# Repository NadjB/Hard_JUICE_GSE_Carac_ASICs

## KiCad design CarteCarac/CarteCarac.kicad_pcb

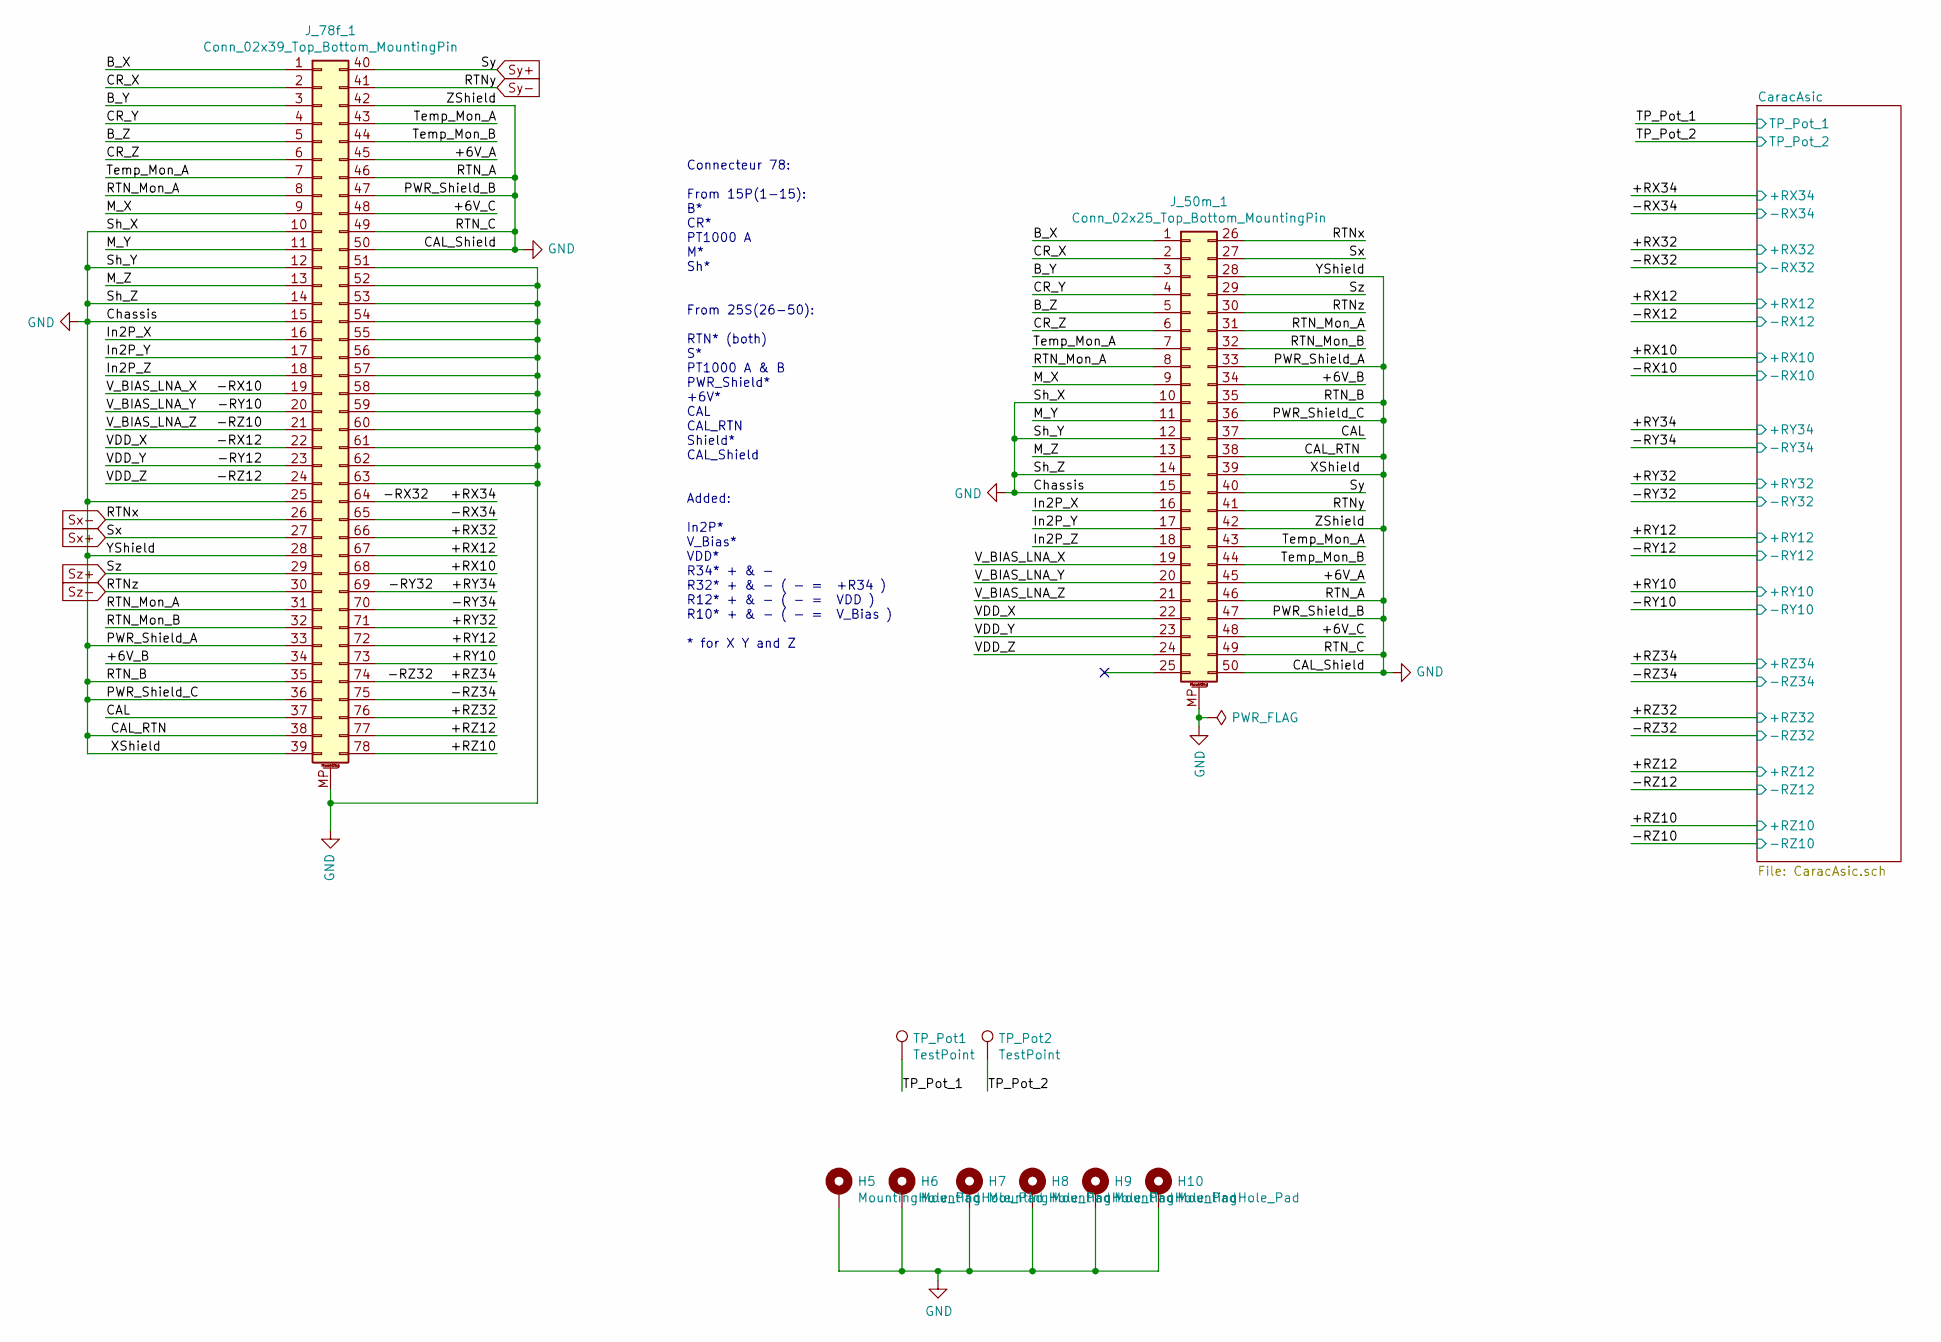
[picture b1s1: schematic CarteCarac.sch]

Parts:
H5, H6, H7, H8, H9, H10: MountingHole_Pad; MountingHole_3.2mm_M3_Pad_Via
J_50m_1: Conn_02x25_Top_Bottom_MountingPin; db_50m_MP_DD50S564TXLF
J_78f_1: Conn_02x39_Top_Bottom_MountingPin; db_78f_MP_09565527613
TP_Pot1, TP_Pot2: TestPoint; Banana_test_point_4mm

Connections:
/+6V_A: J_50m_1.45, J_78f_1.45
/+6V_B: J_50m_1.34, J_78f_1.34
/+6V_C: J_50m_1.48, J_78f_1.48
/+RX10: J_78f_1.68; also elsewhere on the board
/+RX12: J_78f_1.67; also elsewhere on the board
/+RX32: J_78f_1.66; also elsewhere on the board
/+RX34: J_78f_1.64; also elsewhere on the board
/+RY10: J_78f_1.73; also elsewhere on the board
/+RY12: J_78f_1.72; also elsewhere on the board
/+RY32: J_78f_1.71; also elsewhere on the board
/+RY34: J_78f_1.69; also elsewhere on the board
/+RZ10: J_78f_1.78; also elsewhere on the board
/+RZ12: J_78f_1.77; also elsewhere on the board
/+RZ32: J_78f_1.76; also elsewhere on the board
/+RZ34: J_78f_1.74; also elsewhere on the board
/-RX10: J_50m_1.19, J_78f_1.19; also elsewhere on the board
/-RX12: J_50m_1.22, J_78f_1.22; also elsewhere on the board
/-RX34: J_78f_1.65; also elsewhere on the board
/-RY10: J_50m_1.20, J_78f_1.20; also elsewhere on the board
/-RY12: J_50m_1.23, J_78f_1.23; also elsewhere on the board
/-RY34: J_78f_1.70; also elsewhere on the board
/-RZ10: J_50m_1.21, J_78f_1.21; also elsewhere on the board
/-RZ12: J_50m_1.24, J_78f_1.24; also elsewhere on the board
/-RZ34: J_78f_1.75; also elsewhere on the board
/B_X: J_50m_1.1, J_78f_1.1
/B_Y: J_50m_1.3, J_78f_1.3
/B_Z: J_50m_1.5, J_78f_1.5
/CAL: J_50m_1.37, J_78f_1.37
/CR_X: J_50m_1.2, J_78f_1.2
/CR_Y: J_50m_1.4, J_78f_1.4
/CR_Z: J_50m_1.6, J_78f_1.6
/In2P_X: J_50m_1.16, J_78f_1.16
/In2P_Y: J_50m_1.17, J_78f_1.17
/In2P_Z: J_50m_1.18, J_78f_1.18
/M_X: J_50m_1.9, J_78f_1.9
/M_Y: J_50m_1.11, J_78f_1.11
/M_Z: J_50m_1.13, J_78f_1.13
/RTN_Mon_A: J_50m_1.8, J_50m_1.31, J_78f_1.8, J_78f_1.31
/RTN_Mon_B: J_50m_1.32, J_78f_1.32
/TP_Pot_1: TP_Pot1.1; also elsewhere on the board
/TP_Pot_2: TP_Pot2.1; also elsewhere on the board
/Temp_Mon_A: J_50m_1.7, J_50m_1.43, J_78f_1.7, J_78f_1.43
/Temp_Mon_B: J_50m_1.44, J_78f_1.44
GND: H5.1, H6.1, H7.1, H8.1, H9.1, H10.1, J_50m_1.10, J_50m_1.12, J_50m_1.14, J_50m_1.15, J_50m_1.28, J_50m_1.33, J_50m_1.35, J_50m_1.36, J_50m_1.38, J_50m_1.39, J_50m_1.42, J_50m_1.46, J_50m_1.47, J_50m_1.49, J_50m_1.50, J_50m_1.MP (MountPin), J_78f_1.10, J_78f_1.12, J_78f_1.14, J_78f_1.15, J_78f_1.25, J_78f_1.28, J_78f_1.33, J_78f_1.35, J_78f_1.36, J_78f_1.38, J_78f_1.39, J_78f_1.42, J_78f_1.46, J_78f_1.47, J_78f_1.49, J_78f_1.50, J_78f_1.51, J_78f_1.52, J_78f_1.53, J_78f_1.54, J_78f_1.55, J_78f_1.56, J_78f_1.57, J_78f_1.58, J_78f_1.59, J_78f_1.60, J_78f_1.61, J_78f_1.62, J_78f_1.63, J_78f_1.MP (MountPin); also elsewhere on the board
Sx+: J_50m_1.27, J_78f_1.27
Sx-: J_50m_1.26, J_78f_1.26
Sy+: J_50m_1.40, J_78f_1.40
Sy-: J_50m_1.41, J_78f_1.41
Sz+: J_50m_1.29, J_78f_1.29
Sz-: J_50m_1.30, J_78f_1.30

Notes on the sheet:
Connecteur 78: From 15P(1-15): B* CR* PT1000 A M* Sh* From 25S(26-50): RTN* (both) S* PT1000 A & B PWR_Shield* +6V* CAL CAL_RTN Shield* CAL_Shield Added: In2P* V_Bias* VDD* R34* + & - R32* + & - ( - = +R34 ) R12* + & - ( - = VDD ) R10* + & - ( - = V_Bias ) * for X Y and Z

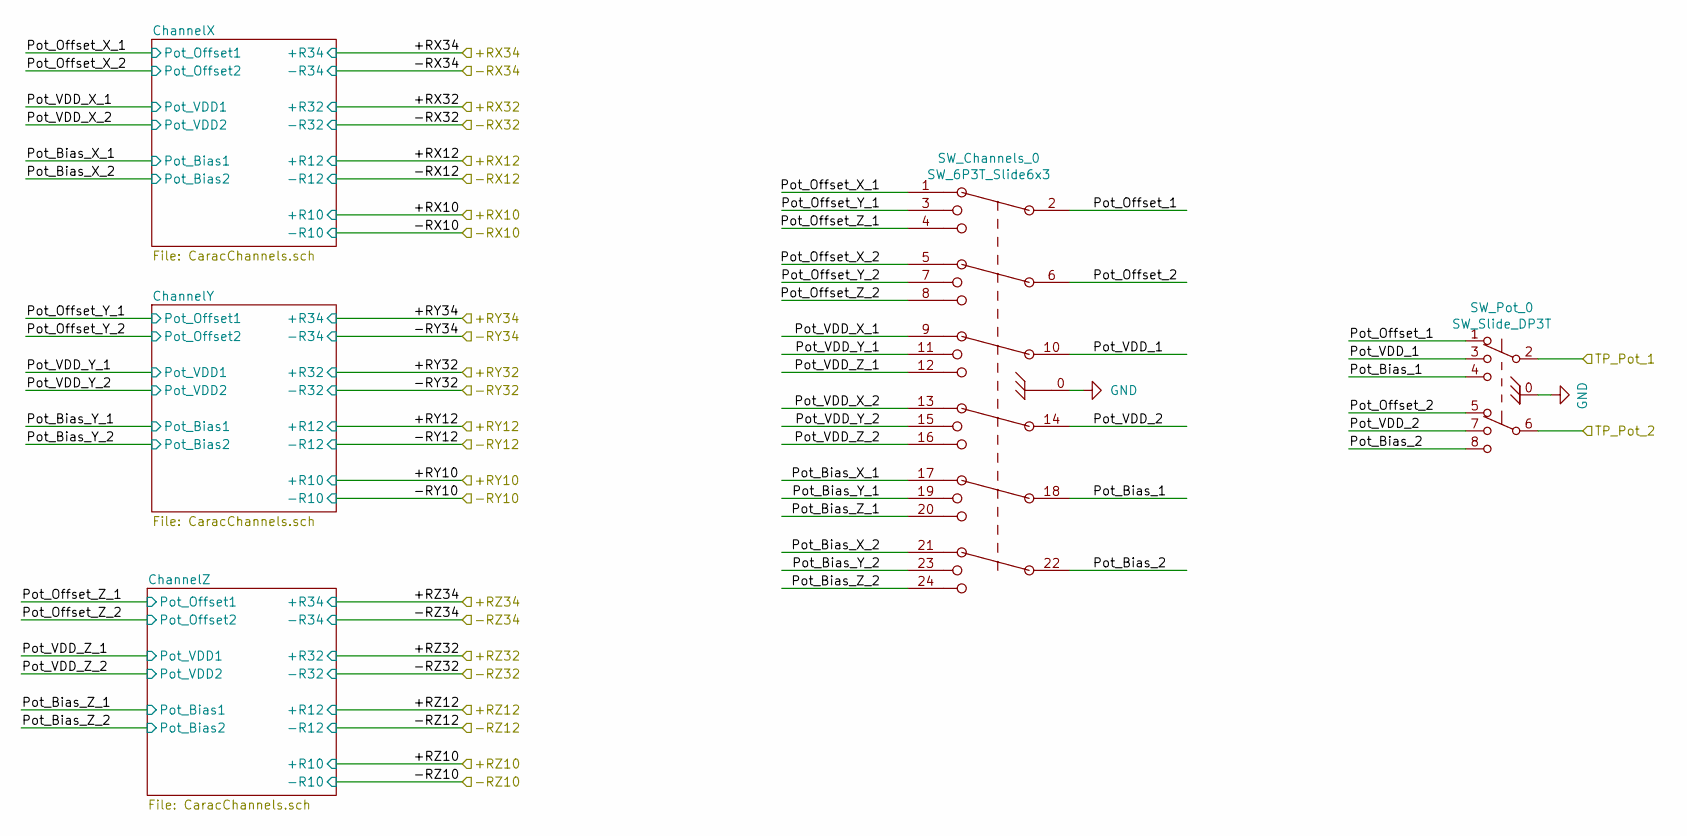
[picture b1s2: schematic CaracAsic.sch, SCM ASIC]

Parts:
SW_Channels_0: SW_6P3T_Slide6x3; SW_6P3T_MSS6350R04_TE
SW_Pot_0: SW_Slide_DP3T; MHS233K_DP3T_Slide_Switch

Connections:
/CaracAsic/Pot_Bias_1: SW_Channels_0.18, SW_Pot_0.4 (D)
/CaracAsic/Pot_Bias_2: SW_Channels_0.22, SW_Pot_0.8 (D)
/CaracAsic/Pot_Bias_X_1: SW_Channels_0.17; also elsewhere on the board
/CaracAsic/Pot_Bias_X_2: SW_Channels_0.21; also elsewhere on the board
/CaracAsic/Pot_Bias_Y_1: SW_Channels_0.19; also elsewhere on the board
/CaracAsic/Pot_Bias_Y_2: SW_Channels_0.23; also elsewhere on the board
/CaracAsic/Pot_Bias_Z_1: SW_Channels_0.20; also elsewhere on the board
/CaracAsic/Pot_Bias_Z_2: SW_Channels_0.24; also elsewhere on the board
/CaracAsic/Pot_Offset_1: SW_Channels_0.2, SW_Pot_0.1 (A)
/CaracAsic/Pot_Offset_2: SW_Channels_0.6, SW_Pot_0.5 (A)
/CaracAsic/Pot_Offset_X_1: SW_Channels_0.1; also elsewhere on the board
/CaracAsic/Pot_Offset_X_2: SW_Channels_0.5; also elsewhere on the board
/CaracAsic/Pot_Offset_Y_1: SW_Channels_0.3; also elsewhere on the board
/CaracAsic/Pot_Offset_Y_2: SW_Channels_0.7; also elsewhere on the board
/CaracAsic/Pot_Offset_Z_1: SW_Channels_0.4; also elsewhere on the board
/CaracAsic/Pot_Offset_Z_2: SW_Channels_0.8; also elsewhere on the board
/CaracAsic/Pot_VDD_1: SW_Channels_0.10, SW_Pot_0.3 (B)
/CaracAsic/Pot_VDD_2: SW_Channels_0.14, SW_Pot_0.7 (B)
/CaracAsic/Pot_VDD_X_1: SW_Channels_0.9; also elsewhere on the board
/CaracAsic/Pot_VDD_X_2: SW_Channels_0.13; also elsewhere on the board
/CaracAsic/Pot_VDD_Y_1: SW_Channels_0.11; also elsewhere on the board
/CaracAsic/Pot_VDD_Y_2: SW_Channels_0.15; also elsewhere on the board
/CaracAsic/Pot_VDD_Z_1: SW_Channels_0.12; also elsewhere on the board
/CaracAsic/Pot_VDD_Z_2: SW_Channels_0.16; also elsewhere on the board
/TP_Pot_1: SW_Pot_0.2 (C); also elsewhere on the board
/TP_Pot_2: SW_Pot_0.6 (C); also elsewhere on the board
GND: SW_Channels_0.0, SW_Pot_0.0 (Casing); also elsewhere on the board

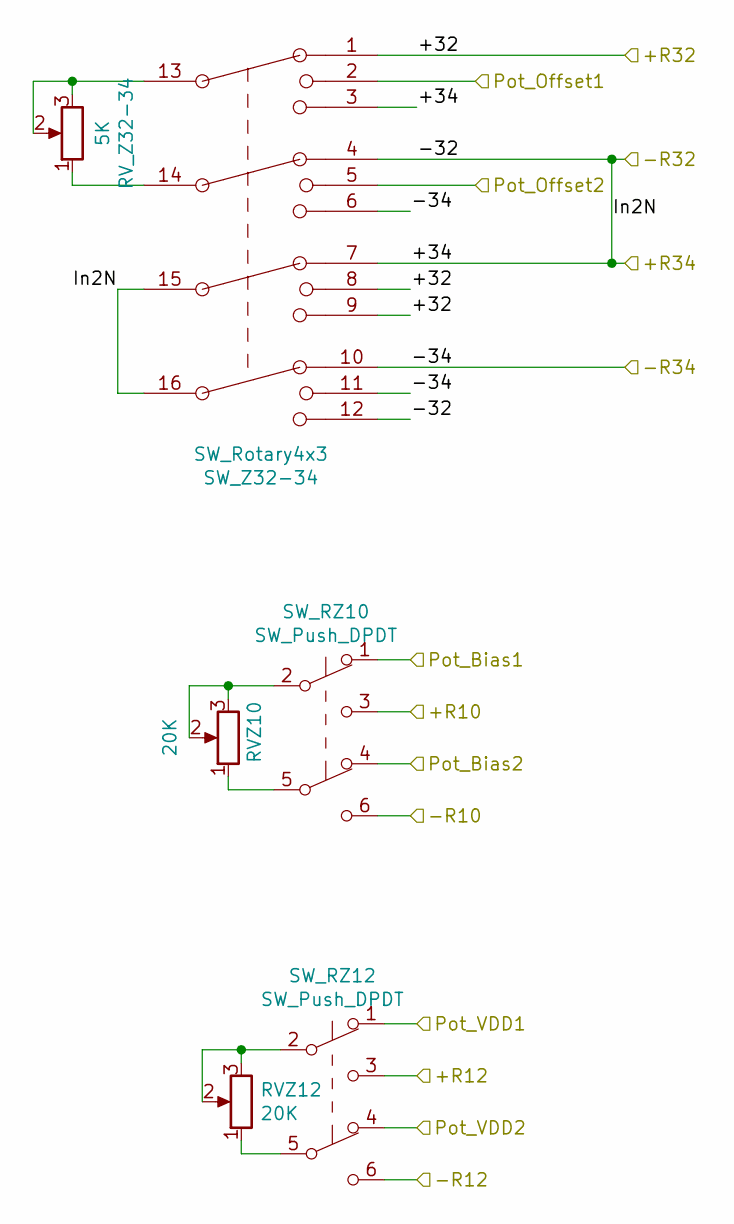
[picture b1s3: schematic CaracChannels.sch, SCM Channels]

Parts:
RVX10, RVX12: 20K; Potentiometer_Bourns_3683S
RV_X32-34: 5K; Potentiometer_Bourns_3683S
SW_RX10, SW_RX12: SW_Push_DPDT; SW_NKK_DPDT_B22AP
SW_X32-34: SW_Rotary4x3; Switch_4P3T_MRA403_NKK_Turned30°

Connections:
/+RX10: SW_RX10.3 (C); also elsewhere on the board
/+RX12: SW_RX12.3 (C); also elsewhere on the board
/+RX32: SW_X32-34.1, SW_X32-34.8, SW_X32-34.9; also elsewhere on the board
/+RX34: SW_X32-34.3, SW_X32-34.4, SW_X32-34.7, SW_X32-34.12, SW_X32-34.15, SW_X32-34.16; also elsewhere on the board
/-RX10: SW_RX10.6 (C); also elsewhere on the board
/-RX12: SW_RX12.6 (C); also elsewhere on the board
/-RX34: SW_X32-34.6, SW_X32-34.10, SW_X32-34.11; also elsewhere on the board
/CaracAsic/Pot_Bias_X_1: SW_RX10.1 (A); also elsewhere on the board
/CaracAsic/Pot_Bias_X_2: SW_RX10.4 (A); also elsewhere on the board
/CaracAsic/Pot_Offset_X_1: SW_X32-34.2; also elsewhere on the board
/CaracAsic/Pot_Offset_X_2: SW_X32-34.5; also elsewhere on the board
/CaracAsic/Pot_VDD_X_1: SW_RX12.1 (A); also elsewhere on the board
/CaracAsic/Pot_VDD_X_2: SW_RX12.4 (A); also elsewhere on the board
unnamed: RVX10.1, SW_RX10.5 (B)
unnamed: RVX10.2, RVX10.3, SW_RX10.2 (B)
unnamed: RVX12.1, SW_RX12.5 (B)
unnamed: RVX12.2, RVX12.3, SW_RX12.2 (B)
unnamed: RV_X32-34.1, SW_X32-34.14
unnamed: RV_X32-34.2, RV_X32-34.3, SW_X32-34.13

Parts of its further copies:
RVY10, RVY12: 20K; Potentiometer_Bourns_3683S
RVZ10, RVZ12: 20K; Potentiometer_Bourns_3683S
RV_Y32-34: 5K; Potentiometer_Bourns_3683S
RV_Z32-34: 5K; Potentiometer_Bourns_3683S
SW_RY10, SW_RY12: SW_Push_DPDT; SW_NKK_DPDT_B22AP
SW_RZ10, SW_RZ12: SW_Push_DPDT; SW_NKK_DPDT_B22AP
SW_Y32-34: SW_Rotary4x3; Switch_4P3T_MRA403_NKK_Turned30°
SW_Z32-34: SW_Rotary4x3; Switch_4P3T_MRA403_NKK_Turned30°

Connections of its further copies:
/+RY10: SW_RY10.3 (C); also elsewhere on the board
/+RY12: SW_RY12.3 (C); also elsewhere on the board
/+RY32: SW_Y32-34.1, SW_Y32-34.8, SW_Y32-34.9; also elsewhere on the board
/+RY34: SW_Y32-34.3, SW_Y32-34.4, SW_Y32-34.7, SW_Y32-34.12, SW_Y32-34.15, SW_Y32-34.16; also elsewhere on the board
/+RZ10: SW_RZ10.3 (C); also elsewhere on the board
/+RZ12: SW_RZ12.3 (C); also elsewhere on the board
/+RZ32: SW_Z32-34.1, SW_Z32-34.8, SW_Z32-34.9; also elsewhere on the board
/+RZ34: SW_Z32-34.3, SW_Z32-34.4, SW_Z32-34.7, SW_Z32-34.12, SW_Z32-34.15, SW_Z32-34.16; also elsewhere on the board
/-RY10: SW_RY10.6 (C); also elsewhere on the board
/-RY12: SW_RY12.6 (C); also elsewhere on the board
/-RY34: SW_Y32-34.6, SW_Y32-34.10, SW_Y32-34.11; also elsewhere on the board
/-RZ10: SW_RZ10.6 (C); also elsewhere on the board
/-RZ12: SW_RZ12.6 (C); also elsewhere on the board
/-RZ34: SW_Z32-34.6, SW_Z32-34.10, SW_Z32-34.11; also elsewhere on the board
/CaracAsic/Pot_Bias_Y_1: SW_RY10.1 (A); also elsewhere on the board
/CaracAsic/Pot_Bias_Y_2: SW_RY10.4 (A); also elsewhere on the board
/CaracAsic/Pot_Bias_Z_1: SW_RZ10.1 (A); also elsewhere on the board
/CaracAsic/Pot_Bias_Z_2: SW_RZ10.4 (A); also elsewhere on the board
/CaracAsic/Pot_Offset_Y_1: SW_Y32-34.2; also elsewhere on the board
/CaracAsic/Pot_Offset_Y_2: SW_Y32-34.5; also elsewhere on the board
/CaracAsic/Pot_Offset_Z_1: SW_Z32-34.2; also elsewhere on the board
/CaracAsic/Pot_Offset_Z_2: SW_Z32-34.5; also elsewhere on the board
/CaracAsic/Pot_VDD_Y_1: SW_RY12.1 (A); also elsewhere on the board
/CaracAsic/Pot_VDD_Y_2: SW_RY12.4 (A); also elsewhere on the board
/CaracAsic/Pot_VDD_Z_1: SW_RZ12.1 (A); also elsewhere on the board
/CaracAsic/Pot_VDD_Z_2: SW_RZ12.4 (A); also elsewhere on the board
unnamed: RVY10.1, SW_RY10.5 (B)
unnamed: RVY10.2, RVY10.3, SW_RY10.2 (B)
unnamed: RVY12.1, SW_RY12.5 (B)
unnamed: RVY12.2, RVY12.3, SW_RY12.2 (B)
unnamed: RVZ10.1, SW_RZ10.5 (B)
unnamed: RVZ10.2, RVZ10.3, SW_RZ10.2 (B)
unnamed: RVZ12.1, SW_RZ12.5 (B)
unnamed: RVZ12.2, RVZ12.3, SW_RZ12.2 (B)
unnamed: RV_Y32-34.1, SW_Y32-34.14
unnamed: RV_Y32-34.2, RV_Y32-34.3, SW_Y32-34.13
unnamed: RV_Z32-34.1, SW_Z32-34.14
unnamed: RV_Z32-34.2, RV_Z32-34.3, SW_Z32-34.13

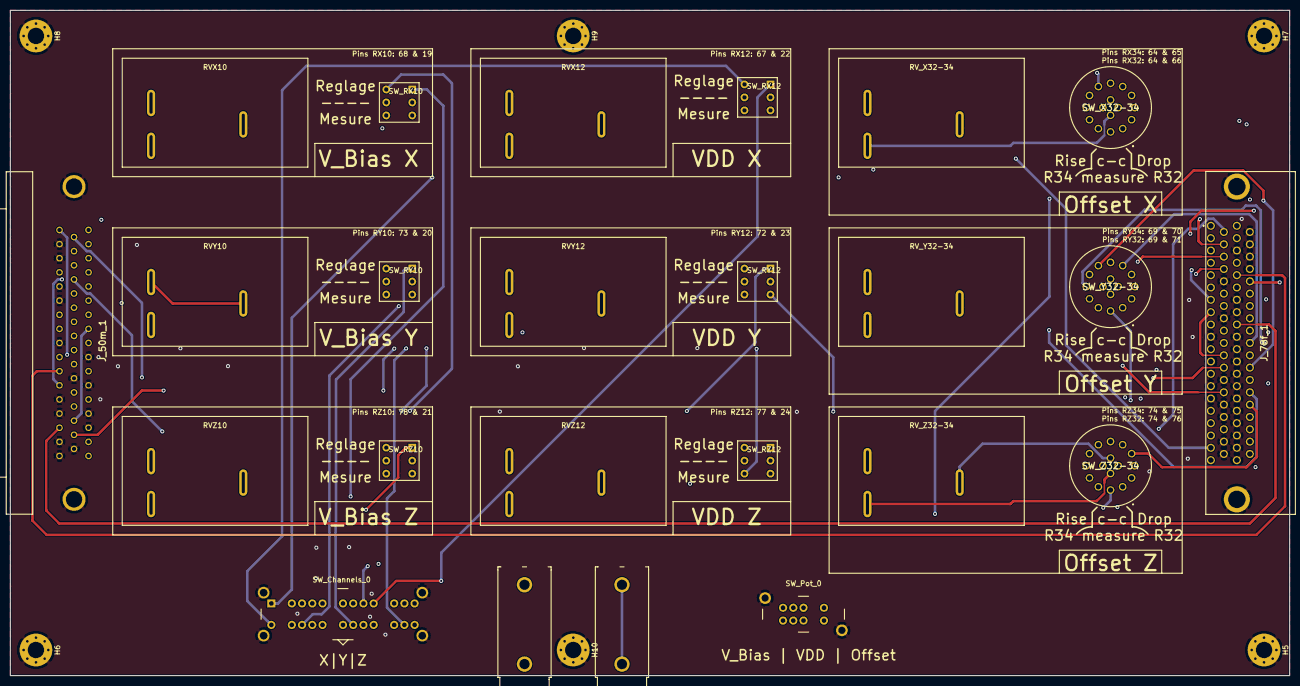
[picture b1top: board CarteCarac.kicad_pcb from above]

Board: 4 copper layers, 250.0 x 130.0 mm, 30 parts (0 on the bottom side), 92 nets.

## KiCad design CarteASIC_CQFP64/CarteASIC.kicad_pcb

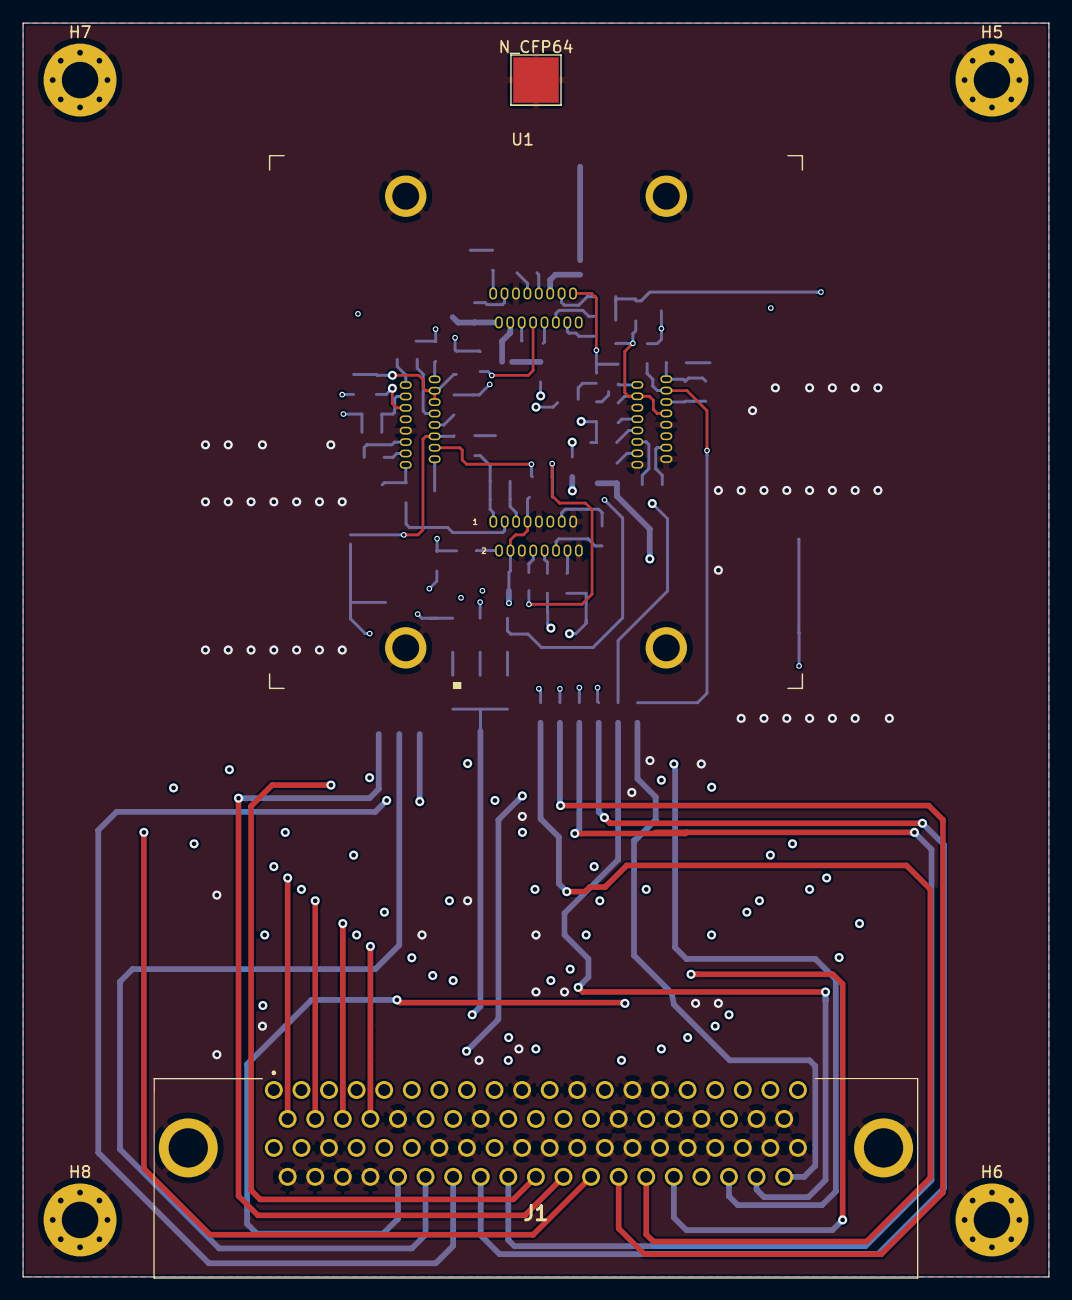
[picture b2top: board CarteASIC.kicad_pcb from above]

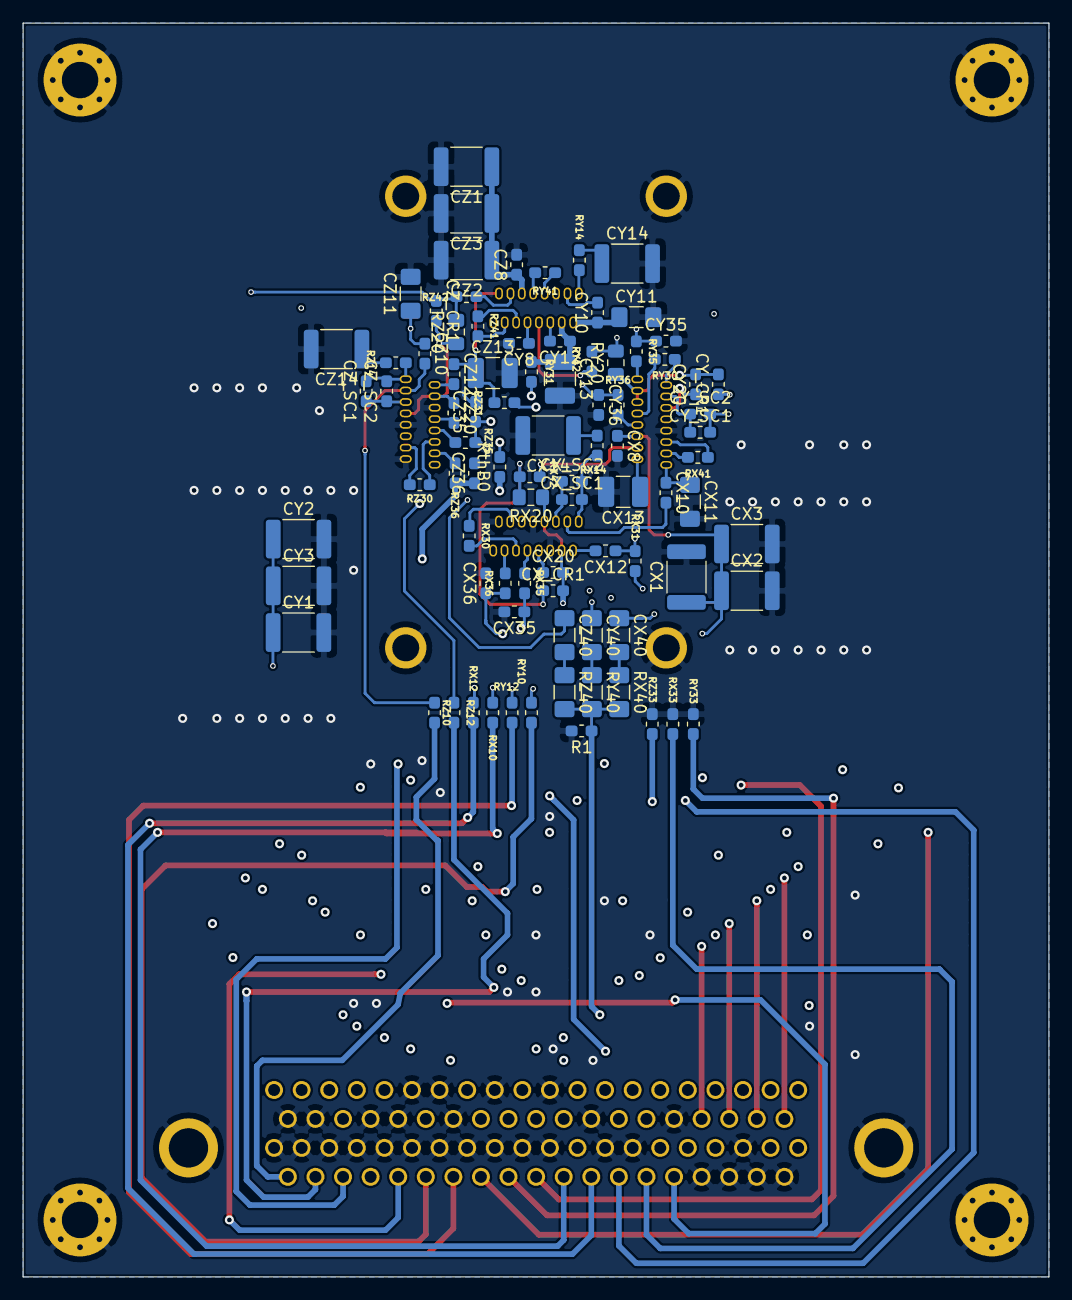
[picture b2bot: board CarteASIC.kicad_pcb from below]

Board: 4 copper layers, 90.0 x 110.0 mm, 93 parts (86 on the bottom side), 84 nets.

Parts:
CX1, CX2, CX3: 680n; C_1812_4532Metric_Pad1.30x3.40mm_HandSolder
CX8: 1n; C_0603_1608Metric_Pad1.05x0.95mm_HandSolder
CX10, CX12: 221p; C_0603_1608Metric_Pad1.05x0.95mm_HandSolder
CX11, CX40: 220n; C_1206_3216Metric_Pad1.42x1.75mm_HandSolder
CX13: 470n; C_1210_3225Metric_Pad1.42x2.65mm_HandSolder
CX14: 470n; C_1812_4532Metric_Pad1.30x3.40mm_HandSolder
CX20, CX35, CX36: *; C_0603_1608Metric_Pad1.05x0.95mm_HandSolder
CX_CR1: 150p; C_0603_1608Metric_Pad1.05x0.95mm_HandSolder
CX_SC1, CX_SC2: *; C_0603_1608Metric_Pad1.05x0.95mm_HandSolder
CY1, CY2, CY3: 680n; C_1812_4532Metric_Pad1.30x3.40mm_HandSolder
CY8: 1n; C_0603_1608Metric_Pad1.05x0.95mm_HandSolder
CY10, CY12: 221p; C_0603_1608Metric_Pad1.05x0.95mm_HandSolder
CY11, CY40: 220n; C_1206_3216Metric_Pad1.42x1.75mm_HandSolder
CY13: 470n; C_1210_3225Metric_Pad1.42x2.65mm_HandSolder
CY14: 470n; C_1812_4532Metric_Pad1.30x3.40mm_HandSolder
CY20, CY35, CY36: *; C_0603_1608Metric_Pad1.05x0.95mm_HandSolder
CY_CR1: 150p; C_0603_1608Metric_Pad1.05x0.95mm_HandSolder
CY_SC1, CY_SC2: *; C_0603_1608Metric_Pad1.05x0.95mm_HandSolder
CZ1, CZ2, CZ3: 680n; C_1812_4532Metric_Pad1.30x3.40mm_HandSolder
CZ8: 1n; C_0603_1608Metric_Pad1.05x0.95mm_HandSolder
CZ10, CZ12: 221p; C_0603_1608Metric_Pad1.05x0.95mm_HandSolder
CZ11, CZ40: 220n; C_1206_3216Metric_Pad1.42x1.75mm_HandSolder
CZ13: 470n; C_1210_3225Metric_Pad1.42x2.65mm_HandSolder
CZ14: 470n; C_1812_4532Metric_Pad1.30x3.40mm_HandSolder
CZ20, CZ35, CZ36: *; C_0603_1608Metric_Pad1.05x0.95mm_HandSolder
CZ_CR1: 150p; C_0603_1608Metric_Pad1.05x0.95mm_HandSolder
CZ_SC1, CZ_SC2: *; C_0603_1608Metric_Pad1.05x0.95mm_HandSolder
H5, H6, H7, H8: MountingHole_Pad; MountingHole_3.2mm_M3_Pad_Via
J1: Conn_02x39_Top_Bottom_MountingPin; db_78m_09565627813
N_CFP64: Housing_Pad; TestPoint_Pad_4.0x4.0mm
R1: 10k; R_0603_1608Metric_Pad1.05x0.95mm_HandSolder
RX10: 22K; R_0603_1608Metric_Pad1.05x0.95mm_HandSolder
RX12: 44K; R_0603_1608Metric_Pad1.05x0.95mm_HandSolder
RX14: 400; R_0603_1608Metric_Pad1.05x0.95mm_HandSolder
RX20: 150k; R_0805_2012Metric_Pad1.15x1.40mm_HandSolder
RX30: 7,68k; R_0603_1608Metric_Pad1.05x0.95mm_HandSolder
RX31, RX33: 49,9k; R_0603_1608Metric_Pad1.05x0.95mm_HandSolder
RX35, RX36: 49,9; R_0603_1608Metric_Pad1.05x0.95mm_HandSolder
RX40: 750k; R_1206_3216Metric_Pad1.42x1.75mm_HandSolder
RX41: 24,9k; R_0603_1608Metric_Pad1.05x0.95mm_HandSolder
RX42: 42,2k; R_0603_1608Metric_Pad1.05x0.95mm_HandSolder
RY10: 22K; R_0603_1608Metric_Pad1.05x0.95mm_HandSolder
RY12: 44K; R_0603_1608Metric_Pad1.05x0.95mm_HandSolder
RY14: 400; R_0603_1608Metric_Pad1.05x0.95mm_HandSolder
RY20: 150k; R_0805_2012Metric_Pad1.15x1.40mm_HandSolder
RY30: 7,68k; R_0603_1608Metric_Pad1.05x0.95mm_HandSolder
RY31, RY33: 49,9k; R_0603_1608Metric_Pad1.05x0.95mm_HandSolder
RY35, RY36: 49,9; R_0603_1608Metric_Pad1.05x0.95mm_HandSolder
RY40: 750k; R_1206_3216Metric_Pad1.42x1.75mm_HandSolder
RY41: 24,9k; R_0603_1608Metric_Pad1.05x0.95mm_HandSolder
RY42: 42,2k; R_0603_1608Metric_Pad1.05x0.95mm_HandSolder
RZ10: 22K; R_0603_1608Metric_Pad1.05x0.95mm_HandSolder
RZ12: 44K; R_0603_1608Metric_Pad1.05x0.95mm_HandSolder
RZ14: 400; R_0603_1608Metric_Pad1.05x0.95mm_HandSolder
RZ20: 150k; R_0805_2012Metric_Pad1.15x1.40mm_HandSolder
RZ30: 7,68k; R_0603_1608Metric_Pad1.05x0.95mm_HandSolder
RZ31, RZ33: 49,9k; R_0603_1608Metric_Pad1.05x0.95mm_HandSolder
RZ35, RZ36: 49,9; R_0603_1608Metric_Pad1.05x0.95mm_HandSolder
RZ40: 750k; R_1206_3216Metric_Pad1.42x1.75mm_HandSolder
RZ41: 24,9k; R_0603_1608Metric_Pad1.05x0.95mm_HandSolder
RZ42: 42,2k; R_0603_1608Metric_Pad1.05x0.95mm_HandSolder
RthB0: PT1000; R_0603_1608Metric_Pad1.05x0.95mm_HandSolder
U1: ASIC_JUICE; 8500-50mm-64T-Ovale-EuroCircuitOK

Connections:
/+6V_A: CX1.1, CX2.1, CX3.1, CX8.1, J1.45, U1.59
/+6V_B: CY1.1, CY2.1, CY3.1, CY8.1, J1.34, U1.39
/+6V_C: CZ1.1, CZ2.1, CZ3.1, CZ8.1, J1.48, U1.38
/+RX10: J1.68, RX10.2
/+RX12: J1.67, RX12.2
/+RX32: J1.66, RX31.1
/+RX34: J1.64, U1.11
/+RY10: J1.73, RY10.2
/+RY12: J1.72, RY12.2
/+RY32: J1.71, RY31.1
/+RY34: J1.69, U1.56
/+RZ10: J1.78, RZ10.2
/+RZ12: J1.77, RZ12.2
/+RZ32: J1.76, RZ31.1
/+RZ34: J1.74, U1.22
/-RX10: CX10.1, CX11.1, J1.19, U1.64
/-RX12: CX12.1, CX13.1, J1.22, RX31.2, U1.63
/-RX34: J1.65, RX33.1
/-RY10: CY10.1, CY11.1, J1.20, U1.47
/-RY12: CY12.1, CY13.1, J1.23, RY31.2, U1.45
/-RY34: J1.70, RY33.1
/-RZ10: CZ10.1, CZ11.1, J1.21, U1.33
/-RZ12: CZ12.1, CZ13.1, J1.24, RZ31.2, U1.34
/-RZ34: J1.75, RZ33.1
/AsicFM/CAL_Gain_X: RX41.1, U1.60
/AsicFM/CAL_Gain_Y: RY41.1, U1.40
/AsicFM/CAL_Gain_Z: RZ41.1, U1.37
/AsicFM/CAL_In_X: CX40.1, RX41.2, U1.62
/AsicFM/CAL_In_Y: CY40.1, RY41.2, U1.42
/AsicFM/CAL_In_Z: CZ40.1, RZ41.2, U1.35
/AsicFM/CAL_Out_X: RX42.1, U1.61
/AsicFM/CAL_Out_Y: RY42.1, U1.41
/AsicFM/CAL_Out_Z: RZ42.1, U1.36
/AsicFM/Gain_Out2_N_X: RX30.2, U1.12
/AsicFM/Gain_Out2_N_Y: RY30.2, U1.55
/AsicFM/Gain_Out2_N_Z: RZ30.2, U1.21
/AsicFM/Gain_Out2_P_X: RX30.1, U1.13
/AsicFM/Gain_Out2_P_Y: RY30.1, U1.50
/AsicFM/Gain_Out2_P_Z: RZ30.1, U1.20
/AsicFM/In1N_X: CX20.1, U1.8
/AsicFM/In1N_Y: CY20.1, U1.54
/AsicFM/In1N_Z: CZ20.1, U1.25
/AsicFM/Out2_NInv_X: RX35.2, U1.10
/AsicFM/Out2_NInv_Y: RY35.2, U1.49
/AsicFM/Out2_NInv_Z: RZ35.2, U1.23
/AsicFM/Out2_inv_X: RX36.2, U1.14
/AsicFM/Out2_inv_Y: RY36.2, U1.57
/AsicFM/Out2_inv_Z: RZ36.2, U1.19
/AsicFM/Regu_Bias_LNA_X: CX10.2, RX10.1, U1.3
/AsicFM/Regu_Bias_LNA_Y: CY10.2, RY10.1, U1.46
/AsicFM/Regu_Bias_LNA_Z: CZ10.2, RZ10.1, U1.30
/AsicFM/Regu_VDD_X: CX12.2, RX12.1, U1.2
/AsicFM/Regu_VDD_Y: CY12.2, RY12.1, U1.43
/AsicFM/Regu_VDD_Z: CZ12.2, RZ12.1, U1.31
/B_X: CX_SC1.1, CX_SC2.1, J1.1, U1.5
/B_Y: CY_SC1.1, CY_SC2.1, J1.3, U1.52
/B_Z: CZ_SC1.1, CZ_SC2.1, J1.5, U1.28
/CAL: J1.37, R1.1, RX40.2, RY40.2, RZ40.2
/CR_X: CX_CR1.1, J1.2, RX20.2, RX42.2
/CR_Y: CY_CR1.1, J1.4, RY20.2, RY42.2
/CR_Z: CZ_CR1.1, J1.6, RZ20.2, RZ42.2
/In2P_X: CX20.2, CX_CR1.2, J1.16, RX20.1, U1.4, U1.7
/In2P_Y: CY20.2, CY_CR1.2, J1.17, RY20.1, U1.51, U1.53
/In2P_Z: CZ20.2, CZ_CR1.2, J1.18, RZ20.1, U1.26, U1.29
/M_X: CX_SC1.2, CX_SC2.2, J1.9, RX14.1, U1.1
/M_Y: CY_SC1.2, CY_SC2.2, J1.11, RY14.1, U1.48
/M_Z: CZ_SC1.2, CZ_SC2.2, J1.13, RZ14.1, U1.32
/RTN_Mon_A: J1.8, J1.31
/RTN_Mon_B: J1.32, RthB0.2
/RTNx: CX36.1, J1.26, RX36.1
/RTNy: CY36.1, J1.41, RY36.1
/RTNz: CZ36.1, J1.30, RZ36.1
/Sx: CX35.1, J1.27, RX35.1
/Sy: CY35.1, J1.40, RY35.1
/Sz: CZ35.1, J1.29, RZ35.1
/Temp_Mon_A: J1.7, J1.43
/Temp_Mon_B: J1.44, RthB0.1
GND: CX1.2, CX2.2, CX3.2, CX8.2, CX11.2, CX13.2, CX14.2, CX35.2, CX36.2, CY1.2, CY2.2, CY3.2, CY8.2, CY11.2, CY13.2, CY14.2, CY35.2, CY36.2, CZ1.2, CZ2.2, CZ3.2, CZ8.2, CZ11.2, CZ13.2, CZ14.2, CZ35.2, CZ36.2, H5.1, H6.1, H7.1, H8.1, J1.10, J1.12, J1.14, J1.15, J1.25, J1.28, J1.33, J1.35, J1.36, J1.38, J1.39, J1.42, J1.46, J1.47, J1.49, J1.50, J1.51, J1.52, J1.53, J1.54, J1.55, J1.56, J1.57, J1.58, J1.59, J1.60, J1.61, J1.62, J1.63, J1.MP, N_CFP64.1, R1.2, RX33.2, RY33.2, RZ33.2, U1.6, U1.9, U1.15, U1.16, U1.17, U1.18, U1.24, U1.27, U1.44, U1.58, U1.65, U1.66, U1.67, U1.68
unnamed: CX14.1, RX14.2
unnamed: CX40.2, RX40.1
unnamed: CY14.1, RY14.2
unnamed: CY40.2, RY40.1
unnamed: CZ14.1, RZ14.2
unnamed: CZ40.2, RZ40.1
